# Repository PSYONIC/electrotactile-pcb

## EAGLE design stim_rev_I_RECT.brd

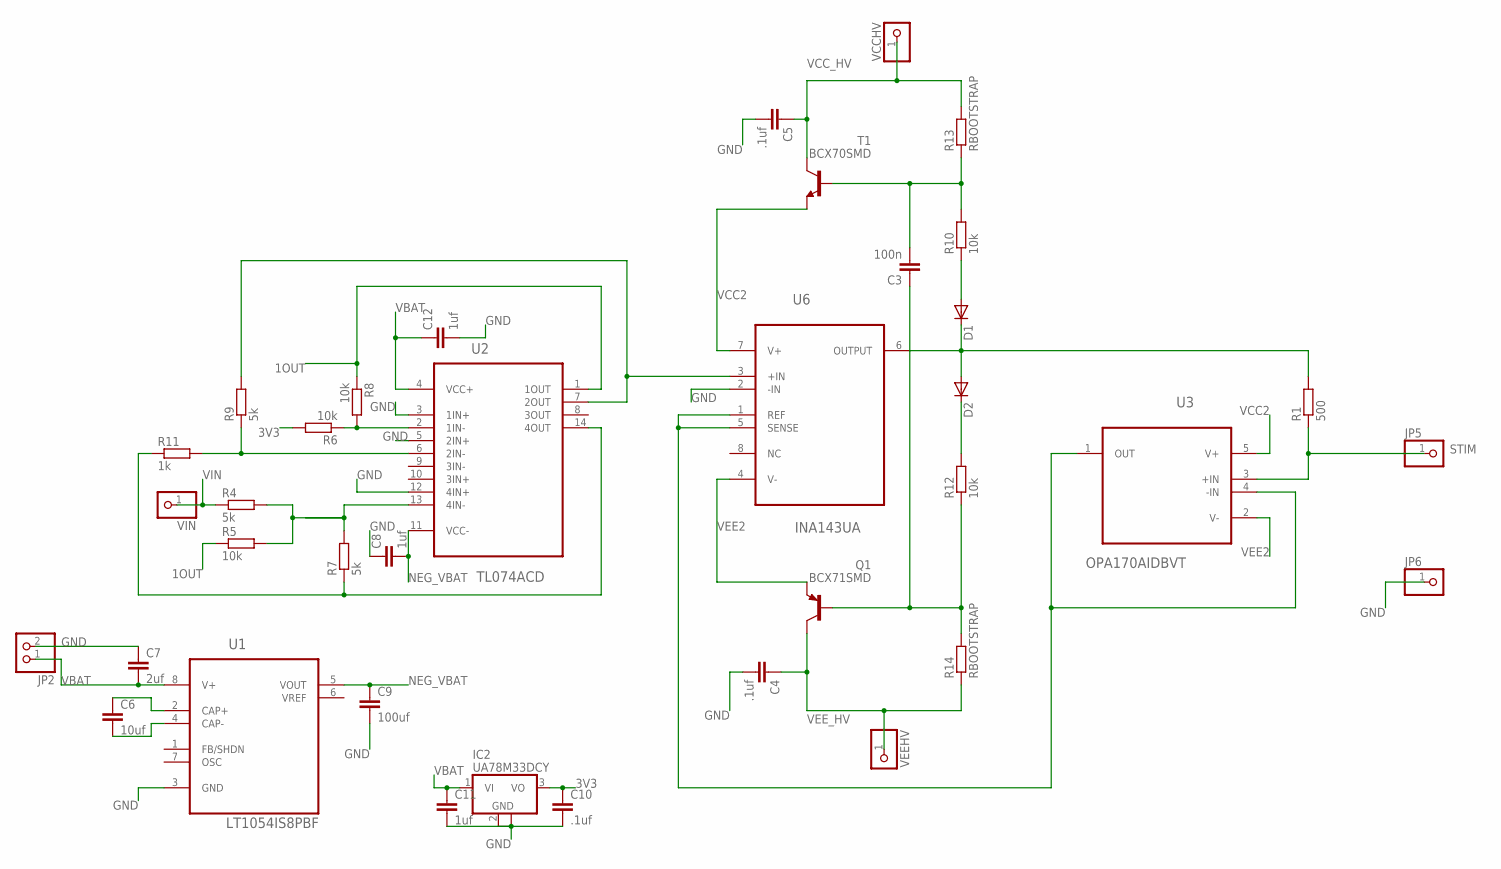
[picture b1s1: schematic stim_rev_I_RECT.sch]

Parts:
C3: 100n; C0603
C4, C5: .1uf; C0603
C6: 10uf; C0603
C7: 2uf; C0603
C8, C11, C12: 1uf; C0603
C9: 100uf; C1210
C10: .1uf; C0402
D1, D2: DIODE-DO214AA; DO214AA
IC2: UA78M33DCY; SOT223
JP2: PINHD-1X2; 1X02
JP5, JP6: PINHD-1X1; 1X01
Q1: BCX71SMD; SOT23
R1: 500; R0603
R4, R7, R9: 5k; R0402
R5, R6, R8: 10k; R0402
R10, R12: 10k; R0603
R11: 1k; R0402
R13, R14: RBOOTSTRAP; R0603
T1: BCX70SMD; SOT23
U1: LT1054IS8PBF; SOIC127P600X175-8N
U2: TL074ACD; SOIC127P600X175-14N
U3: OPA170AIDBVT; SOT95P280X145-5N
U6: INA143UA; SOIC127P600X175-8N
VCCHV: PINHD-1X1; 1X01
VEEHV: PINHD-1X1; 1X01
VIN: PINHD-1X1; 1X01

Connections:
1OUT: R5.1, R8.1, U2.1 (1OUT)
3V3: C10.1, IC2.3 (VO), R6.2
4OUT: R7.1, R11.1, U2.14 (4OUT)
GND: C4.2, C5.2, C7.1, C8.1, C9.2, C10.2, C11.2, C12.2, IC2.2 (GND), IC2.4 (GND), JP2.2, JP6.1, U1.3 (GND), U2.3 (1IN+), U2.5 (2IN+), U2.12 (4IN+), U6.2 (-IN)
unnamed: D1.C, D2.A, R1.2, U6.6 (OUTPUT)
unnamed: C3.1, Q1.1 (B), R12.1, R14.2
unnamed: D2.C, R12.2
unnamed: D1.A, R10.1
unnamed: C3.2, R10.2, R13.1, T1.1 (B)
unnamed: C6.2, U1.4 (CAP-)
unnamed: C6.1, U1.2 (CAP+)
unnamed: R6.1, R8.2, U2.2 (1IN-)
unnamed: R9.1, R11.2, U2.6 (2IN-)
unnamed: U3.1 (OUT), U3.4 (-IN), U6.1 (REF), U6.5 (SENSE)
unnamed: R4.2, R5.2, R7.2, U2.13 (4IN-)
NEG_VBAT: C8.2, C9.1, U1.5 (VOUT), U2.11 (VCC-)
STIM: JP5.1, R1.1, U3.3 (+IN)
VBAT: C7.2, C11.1, C12.1, IC2.1 (VI), JP2.1, U1.8 (V+), U2.4 (VCC+)
VCC2: T1.2 (E), U3.5 (V+), U6.7 (V+)
VCCS_IN: R9.2, U2.7 (2OUT), U6.3 (+IN)
VCC_HV: C5.1, R13.2, T1.3 (C), VCCHV.1
VEE2: Q1.2 (E), U3.2 (V-), U6.4 (V-)
VEE_HV: C4.1, Q1.3 (C), R14.1, VEEHV.1
VIN: R4.1, VIN.1

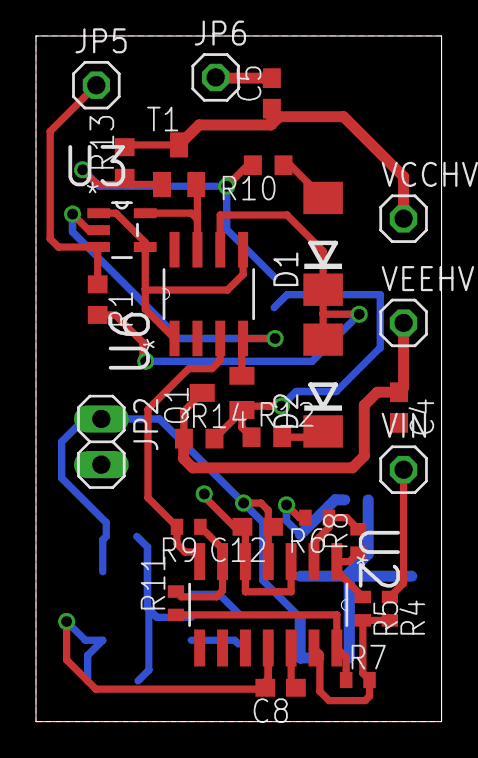
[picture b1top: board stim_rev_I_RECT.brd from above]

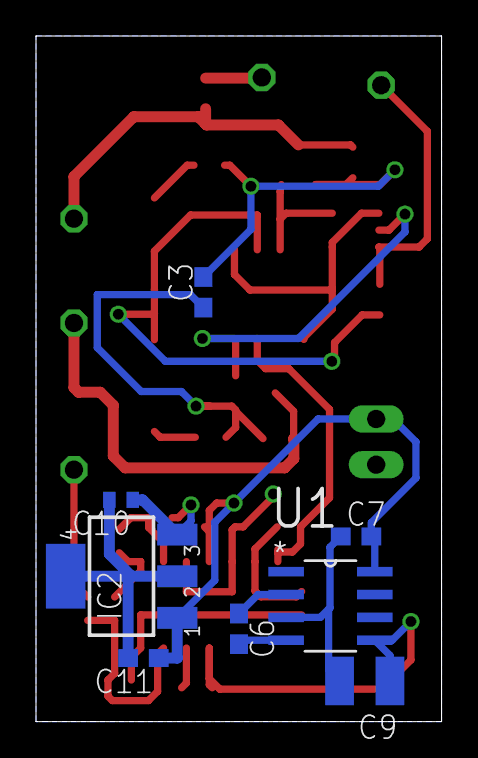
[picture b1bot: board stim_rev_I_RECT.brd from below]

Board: 2 copper layers, 22.5 x 38.1 mm, 37 parts (8 on the bottom side), 24 nets.

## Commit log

2016-10-07 First
    first commit
